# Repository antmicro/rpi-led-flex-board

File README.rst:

===========================
Raspberry Pi LED Flex Board
===========================

Copyright (c) 2022 `Antmicro <https://www.antmicro.com>`_

.. figure:: img/rpi-led-flex-board.jpg

Overview
--------

This repository contains open hardware design files of the LED flexible PCB designed for Raspberry Pi.
It includes a `PCA9685BS <https://www.nxp.com/products/power-management/lighting-driver-and-controller-ics/ic-led-controllers/16-channel-12-bit-pwm-fm-plus-ic-bus-led-controller:PCA9685>`_ GPIO expander which drives five RGB LEDs. 
The GPIO expander is connected to the Raspberry PI over an I2C interface exposed on the camera connector.
This board has been developed and tested with Raspberry Pi 4B.
It has been developed as a part of a compute cluster and fits mechanically in the Open Hardware `Raspberry Pi enclosure <https://github.com/antmicro/rpi-compute-cluster-enclosure>`_.

The design files were prepared in KiCad.
The PCB stackup definition assumes a polyimide, flexible PCB with FR4 stiffeners below the LEDs and the FFC end. 

Repository structure
--------------------
The main repository directory contains KiCad PCB project files, a LICENSE and README.
The remaining files are stored in the following directories:

* ``lib`` - contains the component libraries
* ``img`` - contains graphics for this README

Key features
------------
* 5 x RGB LEDs
* Independent PWM control of the light intensity of each RGB channel in each LED
* I2C communication with Raspberry Pi
* Fits a 15-pin Raspberry Pi camera connector 

License
=======

`Apache-2.0 <LICENSE>`_

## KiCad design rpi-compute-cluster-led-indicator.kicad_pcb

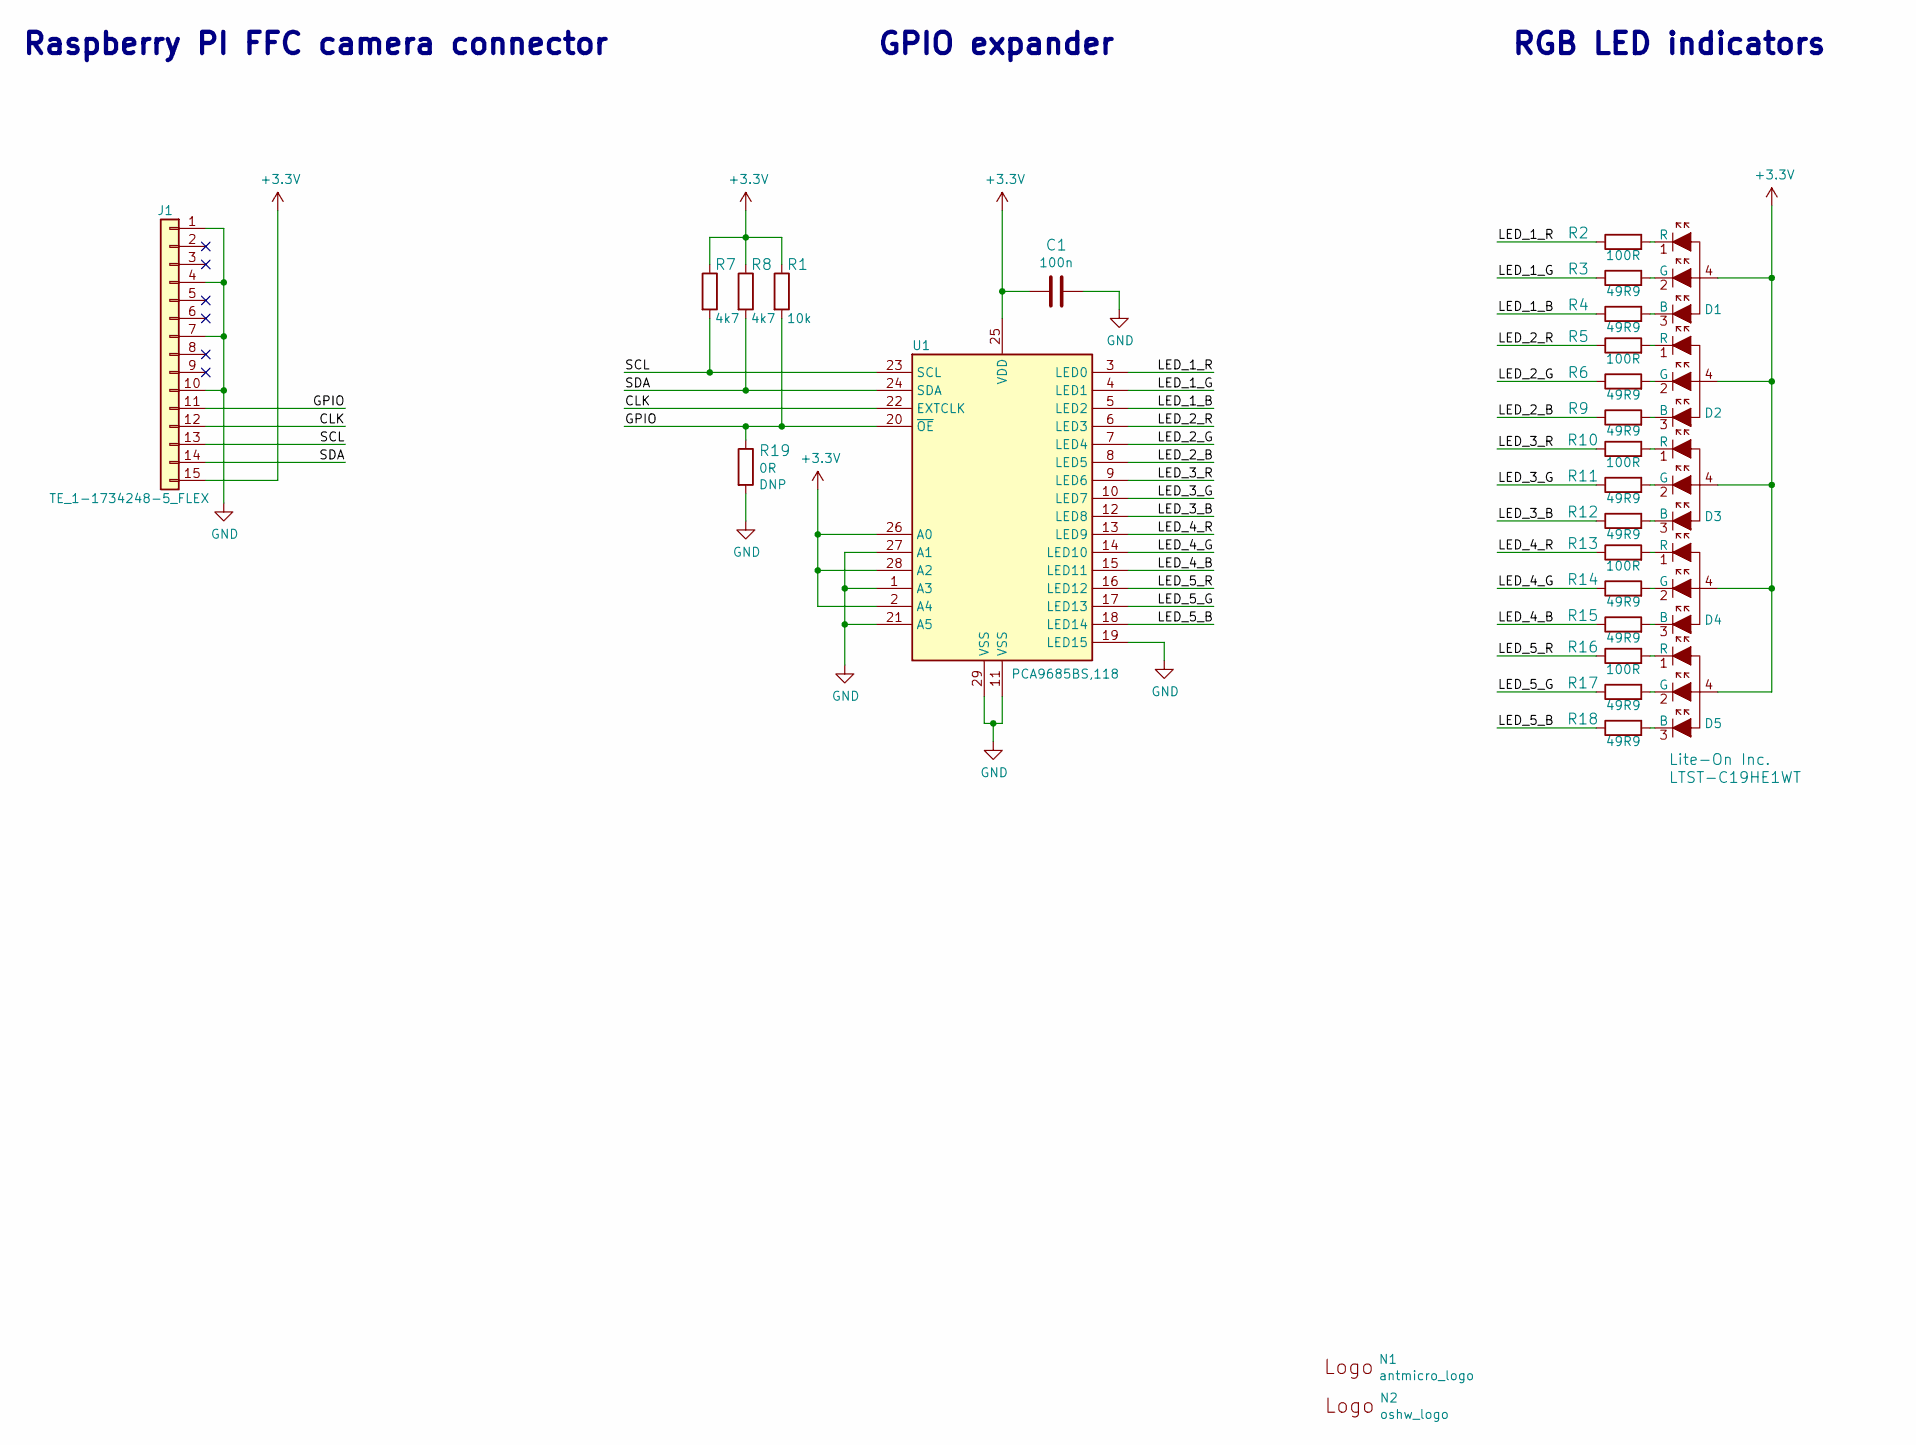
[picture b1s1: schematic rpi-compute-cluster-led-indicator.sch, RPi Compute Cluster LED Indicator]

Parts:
C1: C_100n_0402; 0402-cap; MPN 0402X104K6R3CT
D1, D2, D3, D4, D5: LTST-C19HE1WT; LED_Dual0603; MPN LTST-C19HE1WT
J1: TE_1-1734248-5_FLEX; MPN 1-1734248-5
N1: antmicro_logo; antmicro-logo_scaled_15mm_silk
N2: oshw_logo; OSHW-Logo_5.7x6mm_SilkScreen
R1: R_10k_0402; 0402-res; MPN CRCW040210K0FKEDHP
R2, R5, R10, R13, R16: R_100R_0402; 0402-res; MPN CR0402-FX-1000GLF
R3, R4, R6, R9, R11, R12, R14, R15, R17, R18: R_49R9_0402; 0402-res; MPN CRCW040249R9FKED
R7, R8: R_4k7_0402; 0402-res; MPN ERJ2GEJ472X
R19: R_0R_0402; 0402-res; MPN ERJ2GE0R00X
U1: PCA9685BS,118; QFN-28_6x6mm_P0.65mm

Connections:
+3V3: C1.2, D1.4, D2.4, D3.4, D4.4, D5.4, J1.15, R1.1, R7.1, R8.1, U1.2 (A4), U1.25 (VDD), U1.26 (A0), U1.28 (A2)
/CLK: J1.12, U1.22 (EXTCLK)
/GPIO: J1.11, R1.2, R19.1, U1.20 (~OE)
/LED_1_B: R4.1, U1.5 (LED2)
/LED_1_G: R3.1, U1.4 (LED1)
/LED_1_R: R2.1, U1.3 (LED0)
/LED_2_B: R9.1, U1.8 (LED5)
/LED_2_G: R6.1, U1.7 (LED4)
/LED_2_R: R5.1, U1.6 (LED3)
/LED_3_B: R12.1, U1.12 (LED8)
/LED_3_G: R11.1, U1.10 (LED7)
/LED_3_R: R10.1, U1.9 (LED6)
/LED_4_B: R15.1, U1.15 (LED11)
/LED_4_G: R14.1, U1.14 (LED10)
/LED_4_R: R13.1, U1.13 (LED9)
/LED_5_B: R18.1, U1.18 (LED14)
/LED_5_G: R17.1, U1.17 (LED13)
/LED_5_R: R16.1, U1.16 (LED12)
/SCL: J1.13, R7.2, U1.23 (SCL)
/SDA: J1.14, R8.2, U1.24 (SDA)
GND: C1.1, J1.1, J1.4, J1.7, J1.10, R19.2, U1.1 (A3), U1.11 (VSS), U1.19 (LED15), U1.21 (A5), U1.27 (A1), U1.29 (VSS)
unnamed: D1.1 (R), R2.2
unnamed: D1.2 (G), R3.2
unnamed: D1.3 (B), R4.2
unnamed: D2.1 (R), R5.2
unnamed: D2.2 (G), R6.2
unnamed: D2.3 (B), R9.2
unnamed: D3.1 (R), R10.2
unnamed: D3.2 (G), R11.2
unnamed: D3.3 (B), R12.2
unnamed: D4.1 (R), R13.2
unnamed: D4.2 (G), R14.2
unnamed: D4.3 (B), R15.2
unnamed: D5.1 (R), R16.2
unnamed: D5.2 (G), R17.2
unnamed: D5.3 (B), R18.2

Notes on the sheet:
RGB LED indicators
GPIO expander
Raspberry PI FFC camera connector

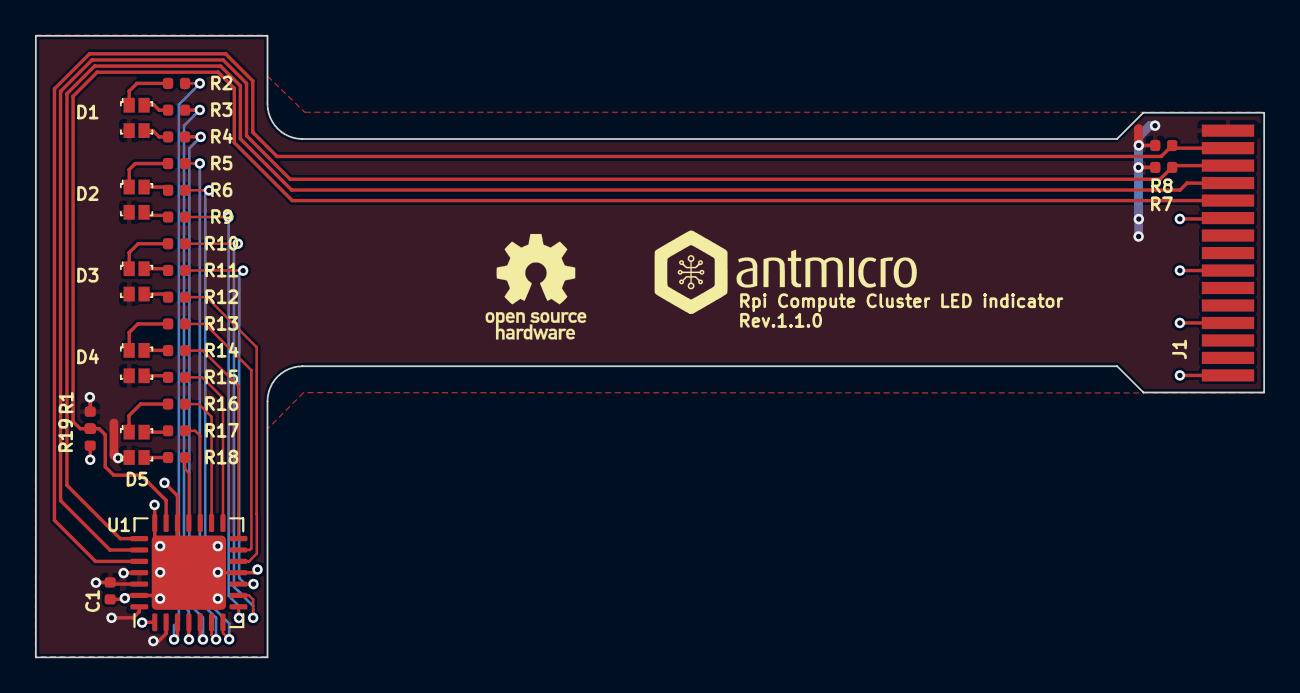
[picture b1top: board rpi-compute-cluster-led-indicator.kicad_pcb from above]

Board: 2 copper layers, 70.3 x 35.6 mm, 29 parts (0 on the bottom side), 36 nets.

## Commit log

2022-03-17 Add LICENSE
2022-03-17 Add the design files
2022-03-17 Add minor fixes
2022-03-17 Add stiffener descriptions
2022-03-17 Add local libraries
2022-03-17 Make flex part thinner
2022-03-17 Restore power supply objects
2022-03-17 Move logos
2022-03-17 Update shape and placement, reroute the PCB
2022-03-17 Update naming convention
2022-03-17 Add dimmensions
2022-03-17 Add 0R DNP resistor at ~OE pin
2022-03-17 Add OSHW Logo
2022-03-17 Separate RPi camera ffc symbol from the GPIO controller
2022-03-17 Assign revision 1.1.0
2022-03-17 Update schematic captions
2022-03-17 README: add link to the GPIO expander
2022-03-17 Updated SDA connection, checked layout, drc-clean
2022-03-17 Add ANT and OSHW logotypes to the sch
2022-03-17 Add README
2022-03-17 README: add link to the RPi enclosure
2022-11-30 README: Add photo
